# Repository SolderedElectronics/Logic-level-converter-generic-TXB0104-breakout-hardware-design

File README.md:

# Logic level converter generic TXB0104 breakout Hardware Design

## About the Product

|  |
| :----------------------------------------------------------: |
| [Buy Logic level converter generic TXB0104 breakout](https://www.solde.red/333017) |

This small and simple module gives us a translation of logic level between two signals. In layman’s terms, if we take a signal with logical “unit” on 5V convert into a signal which logical “unit” has on 3.3V this module will help us. Something like this is useful in this case if we want to achieve communication between two devices from whom one works on 5V and the other on 3.3V, or any other combination of voltages. Directly connecting we would “burn” a device that works on 3.3V and a module gives us to avoid that.

This board is specialized for signal conversion for any communication protocol, and for this conversion, it uses a special integrated circuit that enables communication at high speeds.

---

## Repository Contents

This repository contains all design files for Logic level converter generic TXB0104 breakout, organized as follows:

- **`CAD` folder**: Contains KiCAD design files, including:
  - Schematics
  - PCB layout
  - Panel PCB layout
  - Source 3D files in Fusion360, if any
  - All files are sorted by version with a detailed change log.
- **`OUTPUTS` folder**: Includes all production-ready files, such as:
  - Bill of Materials (BOM) and interactive BOM (iBOM)
  - PDF versions of schematics
  - 3D `.step` file of the board
  - 3D-printable models
  - Gerber files for PCB manufacturing
  - Image of the pinout of the board
  - Product image
  - Compliance, legal and generic sales documents

Refer to the `Change Log` in the CAD folder for details about updates between versions.

---

## Learn More About the Product

Beyond the repository, explore the following resources:

### Soldered Verify

The **Soldered Verify** system ensures every board you purchase from Soldered is fully functional. It also provides access to exclusive test data for your product. To get started, find the unique Soldered Verify ID on your product's packaging and enter the ID on the [Soldered Verify page](https://soldered.com/verify/) to access test results and additional product details.

### Soldered Community

Soldered Community is your go-to place for technical support. Our engineers track and answer all questions posted there, and it’s a great space for the maker community. Get answers to your questions and solutions for your challenges at [Soldered Community](https://soldered.com/community).

### solde.red

solde.red is an ultimate URL shortener and information hub. Access it by typing solde.red/ followed by your product SKU, e.g., [solde.red/333000](https://solde.red/333000), to find getting-started guides, datasheets, open-source hardware and software files, certifications, images, pinouts, and more. Read more about the shortener [here](https://solde.red/info/).

---

## Contributing

Contributions are welcome! Here’s how you can get involved:

- Submit pull requests to enhance the design or fix issues.
- Report bugs or problems by opening an issue.

We encourage community collaboration to make this product even better.

---

## About Soldered

[Soldered for Makers](https://soldered.com) specializes in designing and manufacturing electronic products tailored for enthusiasts, ranging from hobbyists to professionals. Our portfolio includes electronic boards, sensors, and actuators that are widely utilized in fields such as microelectronics, mechatronics, robotics, programming, and IoT. Every product we offer is designed in-house and built upon open-source hardware and software platforms. Proudly certified and manufactured within the European Union, our catalog likely includes the product you need for your project.

We complement these products with comprehensive tutorials and manuals, product descriptions, schematics, programming codes, and project examples. Our round-the-clock [customer and technical support](https://soldered.com/community) is available for all our products, irrespective of the sales channel. Soldered’s success and services reflect our maker community’s unwavering [trust](https://www.trustpilot.com/review/soldered.com), for which we are deeply grateful. Join our community and create using Soldered products.

---

## License

All Soldered open-source hardware (OSH) is under The TAPR Open Hardware License. Read more in the LICENSE file located in this repository.

**Disclaimer:**

No warranty - all designs in this repository are distributed in the hope that they will be useful, but without any warranty. They are provided "AS IS", therefore without warranty of any kind, either expressed or implied. The entire quality and performance of what you do with the contents of this repository are your responsibility. In no event Soldered Electronics will be liable for your damages, or losses, including any general, special, incidental, or consequential damage arising out of the use or inability to use the contents of this repository. 

---

## Have fun!

Thank you for your support from your fellow makers at Soldered Electronics.

Happy Making!

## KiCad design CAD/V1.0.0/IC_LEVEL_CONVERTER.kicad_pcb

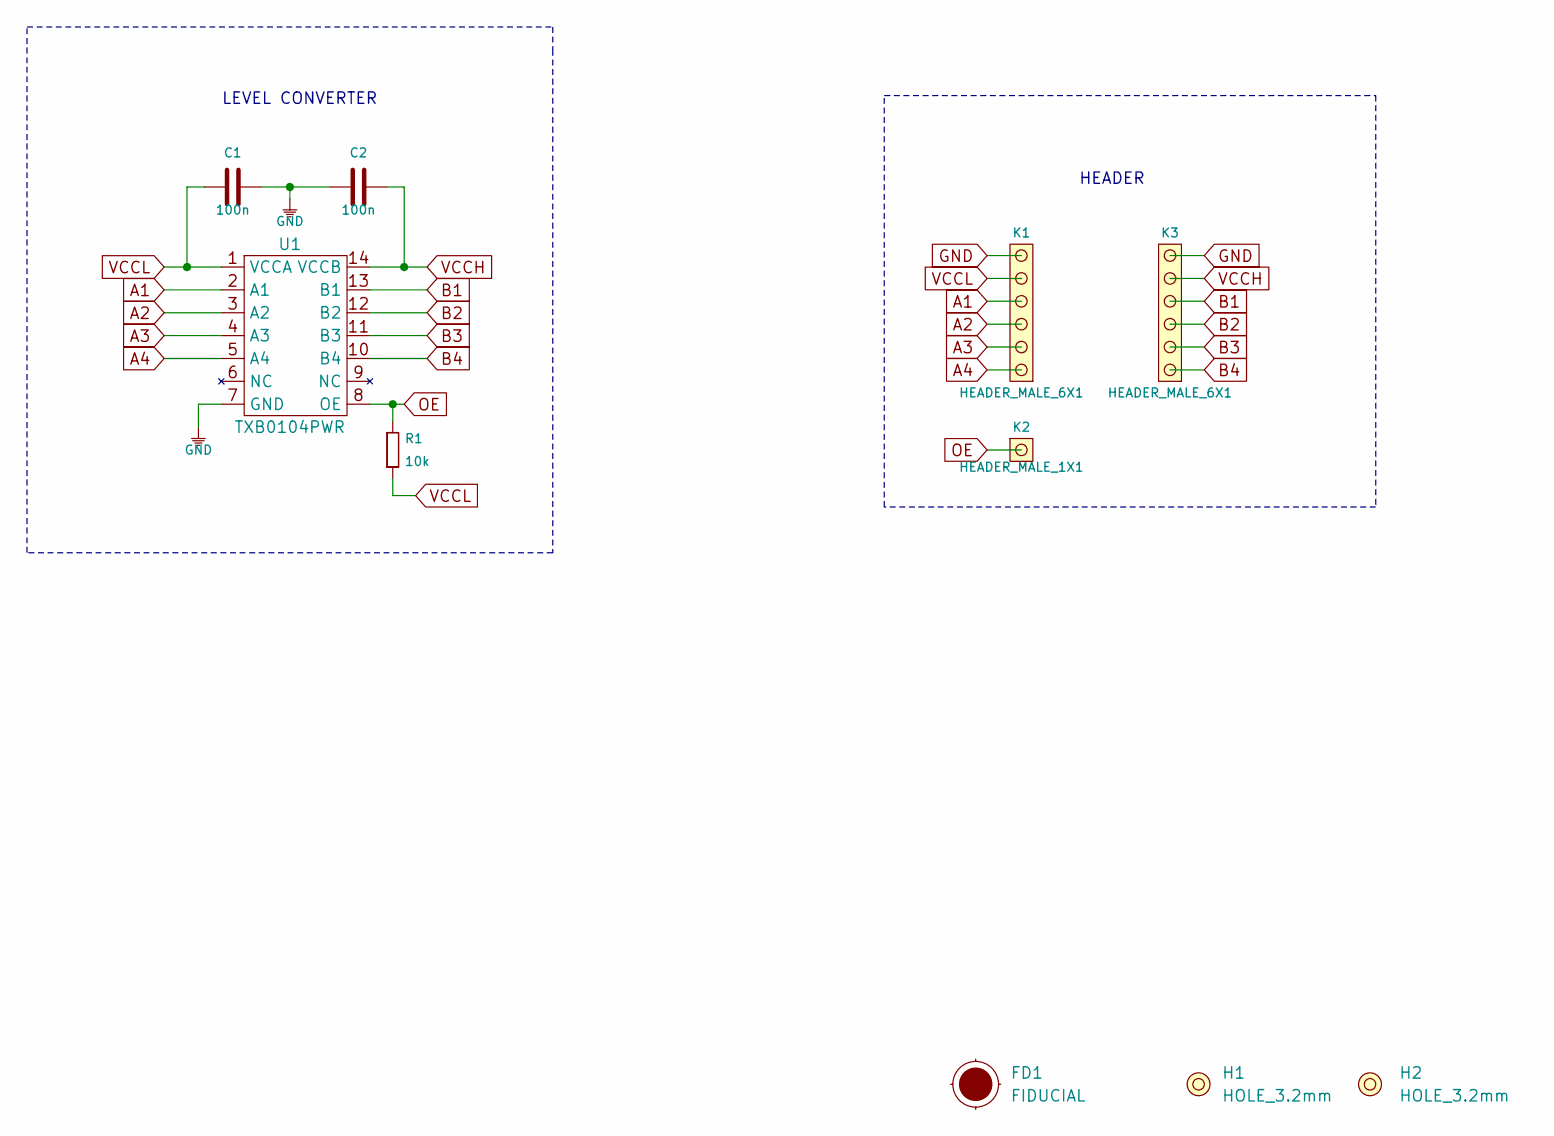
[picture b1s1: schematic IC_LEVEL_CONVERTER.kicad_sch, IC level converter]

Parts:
C1, C2: 100n; 0603C
FD1: FIDUCIAL; FIDUCIAL_23
H1, H2: HOLE_3.2mm
K1, K3: HEADER_MALE_6X1
K2: HEADER_MALE_1X1
R1: 10k; 0603R
U1: TXB0104PWR; TXB0104QPWRQ1

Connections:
A1: K1.4, U1.2 (A1)
A2: K1.3, U1.3 (A2)
A3: K1.2, U1.4 (A3)
A4: K1.1, U1.5 (A4)
B1: K3.4, U1.13 (B1)
B2: K3.3, U1.12 (B2)
B3: K3.2, U1.11 (B3)
B4: K3.1, U1.10 (B4)
GND: C1.2, C2.1, K1.6, K3.6, U1.7 (GND)
OE: K2.1, R1.2, U1.8 (OE)
VCCH: C2.2, K3.5, U1.14 (VCCB)
VCCL: C1.1, K1.5, R1.1, U1.1 (VCCA)

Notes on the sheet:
HEADER
LEVEL CONVERTER

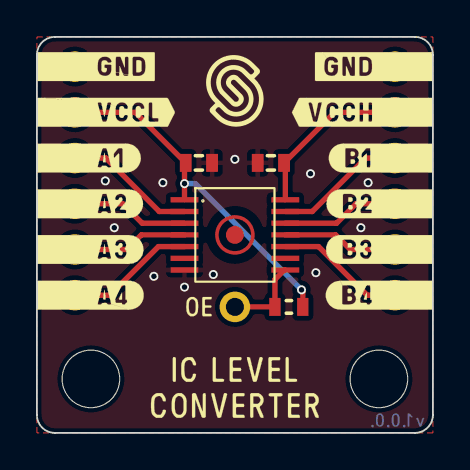
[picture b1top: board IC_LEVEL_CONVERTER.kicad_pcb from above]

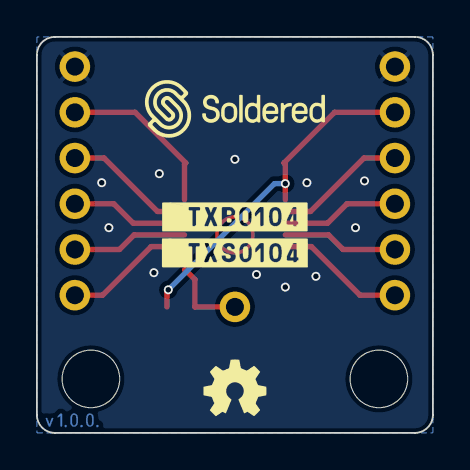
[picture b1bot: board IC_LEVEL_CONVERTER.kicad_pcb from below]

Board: 2 copper layers, 22.0 x 22.0 mm, 10 parts (3 on the bottom side), 12 nets.

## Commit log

2022-08-06 Updating open source files.
